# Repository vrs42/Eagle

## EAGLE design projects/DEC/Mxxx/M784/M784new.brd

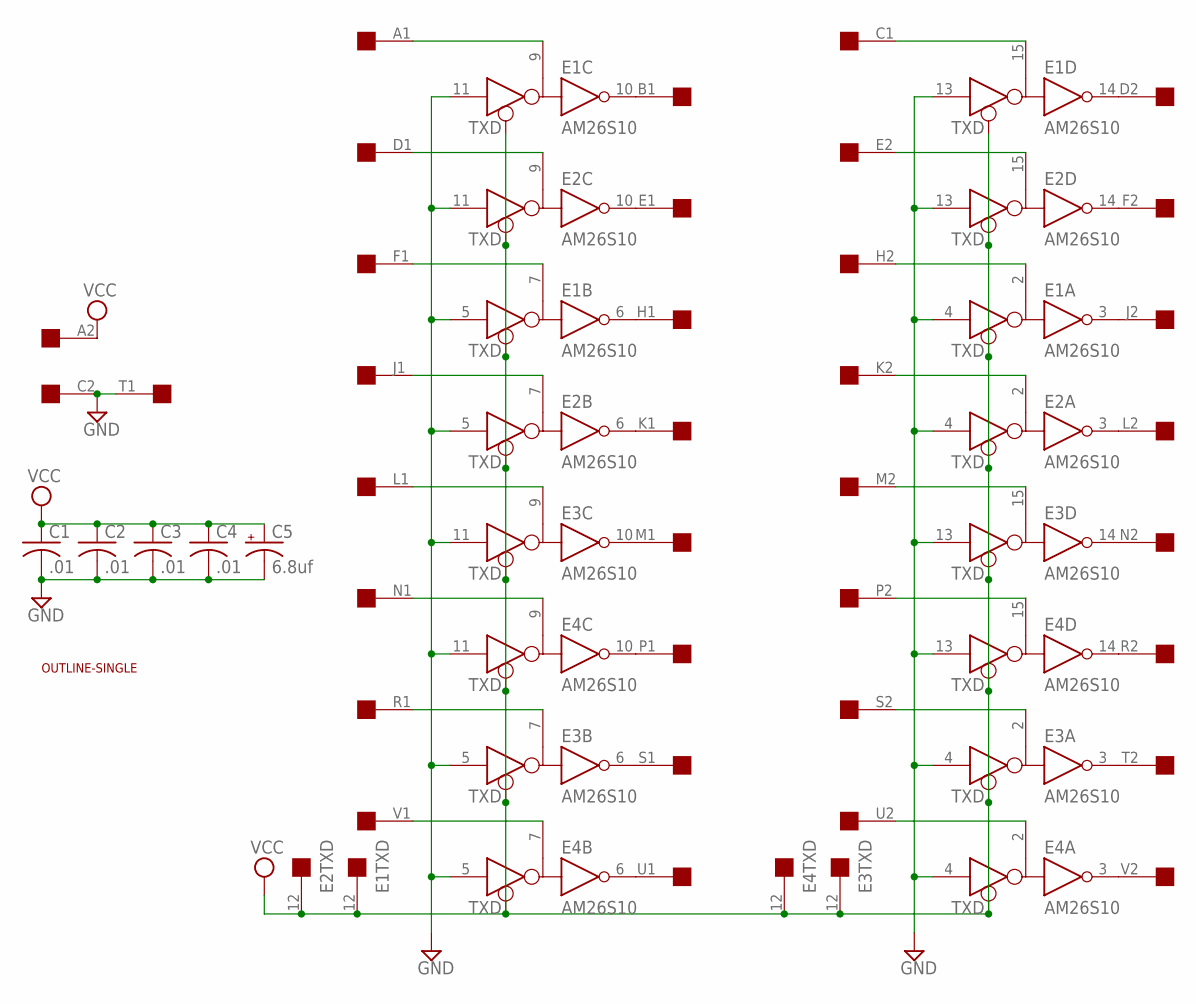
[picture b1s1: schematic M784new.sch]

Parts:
C1, C2, C3, C4: .01; C050-025X075
C5: 6.8uf; E15-5
E1, E2, E3, E4: AM26S10; DIL16
U$1: SINGLE; EDGE-CON2
U$2: OUTLINE-SINGLE; SINGLE

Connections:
GND: C1.2, C2.2, C3.2, C4.2, C5.-, E1.1 (GND), E1.4 (D), E1.5 (D), E1.8 (GND), E1.11 (D), E1.13 (D), E2.1 (GND), E2.4 (D), E2.5 (D), E2.8 (GND), E2.11 (D), E2.13 (D), E3.1 (GND), E3.4 (D), E3.5 (D), E3.8 (GND), E3.11 (D), E3.13 (D), E4.1 (GND), E4.4 (D), E4.5 (D), E4.8 (GND), E4.11 (D), E4.13 (D), U$1.C2, U$1.T1
unnamed: E3.10 (R), U$1.M1
unnamed: E3.9 (B), U$1.L1
unnamed: E2.15 (B), U$1.E2
unnamed: E1.14 (R), U$1.D2
unnamed: E4.9 (B), U$1.N1
unnamed: E1.10 (R), U$1.B1
unnamed: E2.2 (B), U$1.K2
unnamed: E2.10 (R), U$1.E1
unnamed: E2.7 (B), U$1.J1
unnamed: E4.10 (R), U$1.P1
unnamed: E1.6 (R), U$1.H1
unnamed: E4.7 (B), U$1.V1
unnamed: E3.6 (R), U$1.S1
unnamed: E2.14 (R), U$1.F2
unnamed: E3.7 (B), U$1.R1
unnamed: E4.6 (R), U$1.U1
unnamed: E1.15 (B), U$1.C1
unnamed: E1.3 (R), U$1.J2
unnamed: E2.3 (R), U$1.L2
unnamed: E1.2 (B), U$1.H2
unnamed: E3.14 (R), U$1.N2
unnamed: E4.14 (R), U$1.R2
unnamed: E3.3 (R), U$1.T2
unnamed: E4.3 (R), U$1.V2
unnamed: E2.6 (R), U$1.K1
unnamed: E3.15 (B), U$1.M2
unnamed: E4.15 (B), U$1.P2
unnamed: E1.7 (B), U$1.F1
unnamed: E3.2 (B), U$1.S2
unnamed: E2.9 (B), U$1.D1
unnamed: E4.2 (B), U$1.U2
unnamed: E1.9 (B), U$1.A1
VCC: C1.1, C2.1, C3.1, C4.1, C5.+, E1.12 (TXD), E1.16 (VCC), E2.12 (TXD), E2.16 (VCC), E3.12 (TXD), E3.16 (VCC), E4.12 (TXD), E4.16 (VCC), U$1.A2

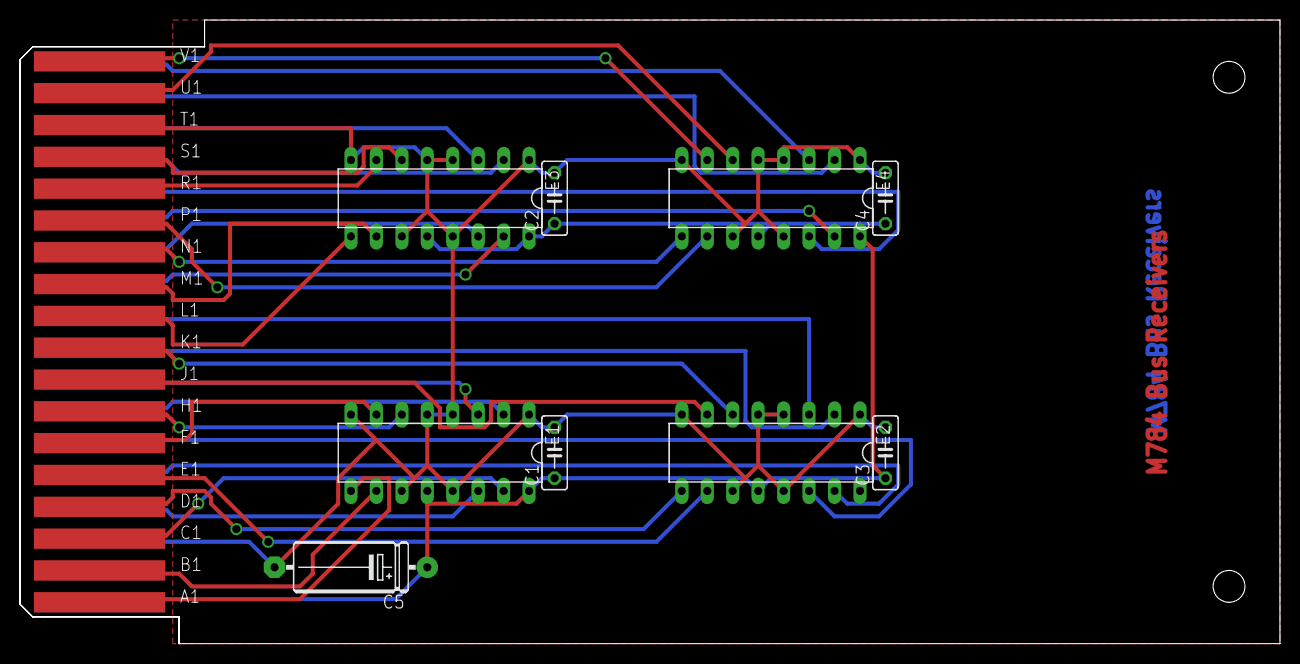
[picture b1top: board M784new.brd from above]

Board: 2 copper layers, 125.7 x 62.2 mm, 11 parts (0 on the bottom side), 34 nets.

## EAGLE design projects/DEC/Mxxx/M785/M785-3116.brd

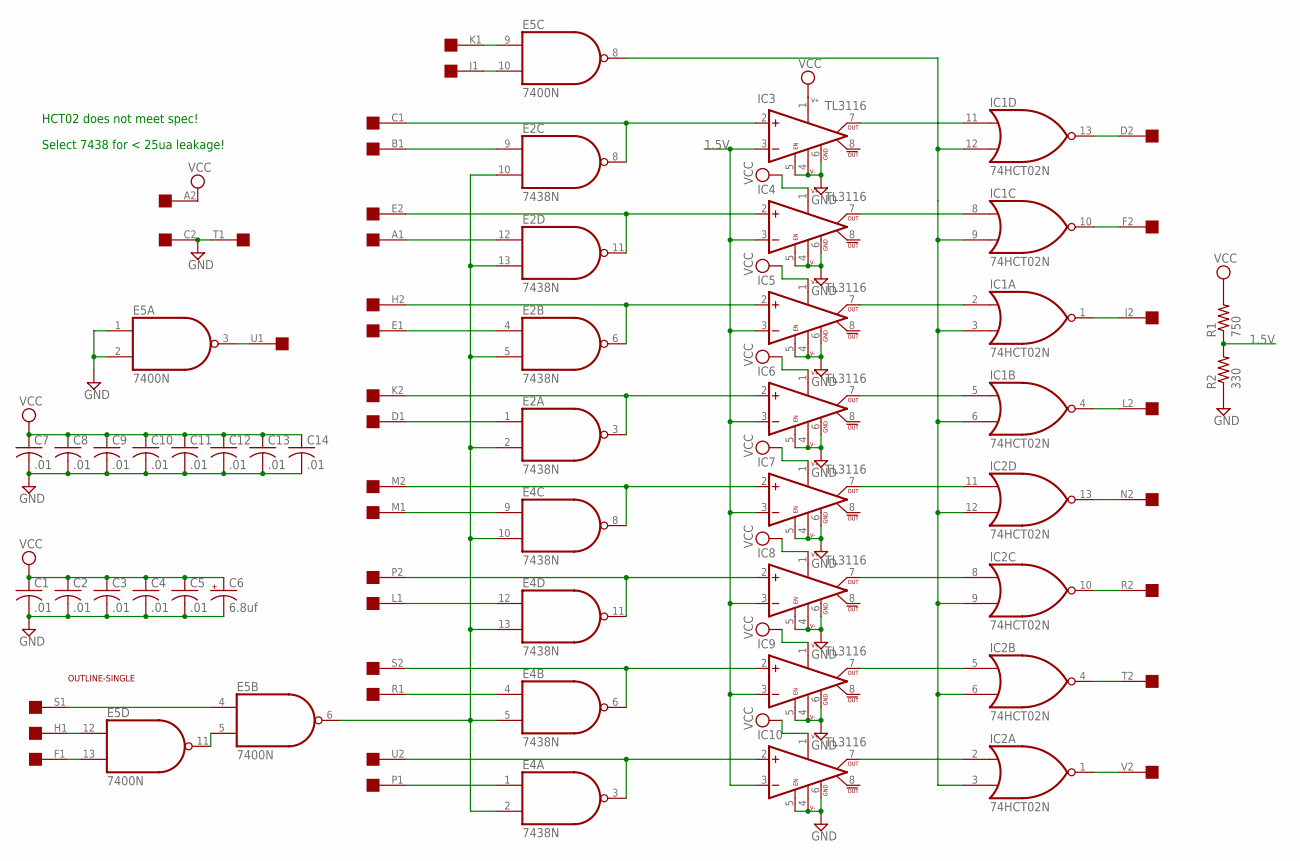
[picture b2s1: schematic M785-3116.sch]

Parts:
C1, C2, C3, C4, C5, C7, C8, C9, C10, C11, C12, C13, C14: .01; C050-025X075
C6: 6.8uf; E15-5
E2, E4: 7438N; DIL14
E5: 7400N; DIL14
IC1, IC2: 74HCT02N; DIL14
IC3, IC4, IC5, IC6, IC7, IC8, IC9, IC10: TL3116; DIL08
R1: 750; 0207/10
R2: 330; 0207/10
U$1: SINGLE; EDGE-CON2
U$2: OUTLINE-SINGLE; SINGLE

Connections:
1.5V: IC3.3 (-IN), IC4.3 (-IN), IC5.3 (-IN), IC6.3 (-IN), IC7.3 (-IN), IC8.3 (-IN), IC9.3 (-IN), IC10.3 (-IN), R1.1, R2.2
GND: C1.2, C2.2, C3.2, C4.2, C5.2, C6.-, C7.2, C8.2, C9.2, C10.2, C11.2, C12.2, C13.2, C14.2, E2.7 (GND), E4.7 (GND), E5.1 (I0), E5.2 (I1), E5.7 (GND), IC1.7 (GND), IC2.7 (GND), IC3.4 (V-), IC3.5 (LA_EN), IC3.6 (GND), IC4.4 (V-), IC4.5 (LA_EN), IC4.6 (GND), IC5.4 (V-), IC5.5 (LA_EN), IC5.6 (GND), IC6.4 (V-), IC6.5 (LA_EN), IC6.6 (GND), IC7.4 (V-), IC7.5 (LA_EN), IC7.6 (GND), IC8.4 (V-), IC8.5 (LA_EN), IC8.6 (GND), IC9.4 (V-), IC9.5 (LA_EN), IC9.6 (GND), IC10.4 (V-), IC10.5 (LA_EN), IC10.6 (GND), R2.1, U$1.C2, U$1.T1
unnamed: E5.8 (O), IC1.3 (I1), IC1.6 (I1), IC1.9 (I1), IC1.12 (I1), IC2.3 (I1), IC2.6 (I1), IC2.9 (I1), IC2.12 (I1)
unnamed: E2.2 (I1), E2.5 (I1), E2.10 (I1), E2.13 (I1), E4.2 (I1), E4.5 (I1), E4.10 (I1), E4.13 (I1), E5.6 (O)
unnamed: E4.8 (O), IC7.2 (+IN), U$1.M2
unnamed: E4.3 (O), IC10.2 (+IN), U$1.U2
unnamed: E4.1 (I0), U$1.P1
unnamed: E4.4 (I0), U$1.R1
unnamed: E4.6 (O), IC9.2 (+IN), U$1.S2
unnamed: E4.12 (I0), U$1.L1
unnamed: E4.11 (O), IC8.2 (+IN), U$1.P2
unnamed: E4.9 (I0), U$1.M1
unnamed: E2.8 (O), IC3.2 (+IN), U$1.C1
unnamed: E2.9 (I0), U$1.B1
unnamed: E2.11 (O), IC4.2 (+IN), U$1.E2
unnamed: E2.12 (I0), U$1.A1
unnamed: E2.6 (O), IC5.2 (+IN), U$1.H2
unnamed: E2.4 (I0), U$1.E1
unnamed: E2.3 (O), IC6.2 (+IN), U$1.K2
unnamed: E2.1 (I0), U$1.D1
unnamed: E5.9 (I0), U$1.K1
unnamed: E5.10 (I1), U$1.J1
unnamed: IC1.13 (O), U$1.D2
unnamed: IC1.10 (O), U$1.F2
unnamed: IC1.1 (O), U$1.J2
unnamed: IC1.4 (O), U$1.L2
unnamed: IC2.13 (O), U$1.N2
unnamed: IC2.10 (O), U$1.R2
unnamed: IC2.4 (O), U$1.T2
unnamed: IC2.1 (O), U$1.V2
unnamed: E5.4 (I0), U$1.S1
unnamed: E5.5 (I1), E5.11 (O)
unnamed: E5.12 (I0), U$1.H1
unnamed: E5.13 (I1), U$1.F1
unnamed: E5.3 (O), U$1.U1
unnamed: IC1.11 (I0), IC3.7 (OUT)
unnamed: IC2.11 (I0), IC7.7 (OUT)
unnamed: IC1.5 (I0), IC6.7 (OUT)
unnamed: IC1.2 (I0), IC5.7 (OUT)
unnamed: IC1.8 (I0), IC4.7 (OUT)
unnamed: IC2.5 (I0), IC9.7 (OUT)
unnamed: IC2.8 (I0), IC8.7 (OUT)
unnamed: IC2.2 (I0), IC10.7 (OUT)
VCC: C1.1, C2.1, C3.1, C4.1, C5.1, C6.+, C7.1, C8.1, C9.1, C10.1, C11.1, C12.1, C13.1, C14.1, E2.14 (VCC), E4.14 (VCC), E5.14 (VCC), IC1.14 (VCC), IC2.14 (VCC), IC3.1 (V+), IC4.1 (V+), IC5.1 (V+), IC6.1 (V+), IC7.1 (V+), IC8.1 (V+), IC9.1 (V+), IC10.1 (V+), R1.2, U$1.A2

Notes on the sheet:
Select 7438 for < 25ua leakage!
HCT02 does not meet spec!

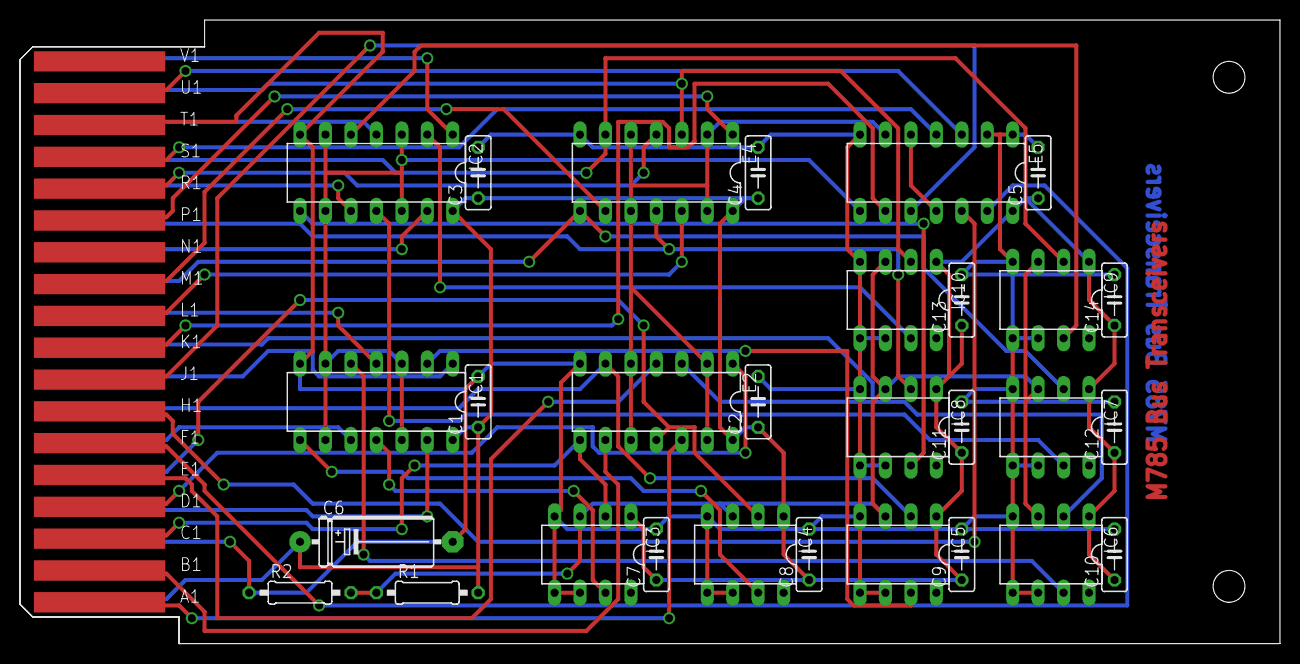
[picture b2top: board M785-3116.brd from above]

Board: 2 copper layers, 125.7 x 62.2 mm, 31 parts (0 on the bottom side), 44 nets.

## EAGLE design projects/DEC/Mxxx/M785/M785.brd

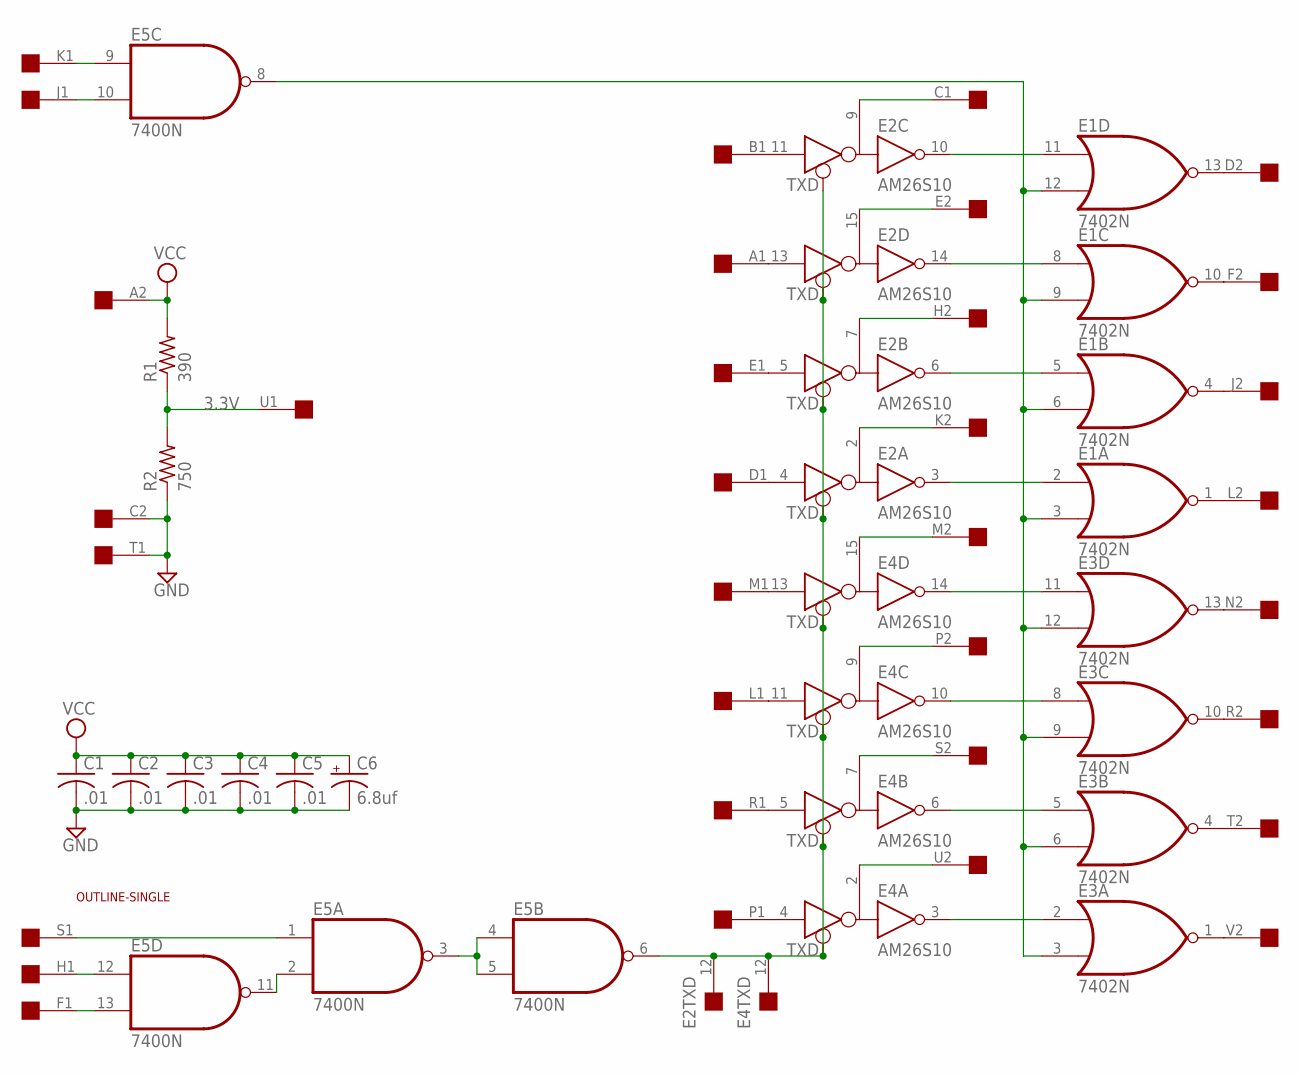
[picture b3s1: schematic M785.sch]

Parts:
C1, C2, C3, C4, C5: .01; C050-025X075
C6: 6.8uf; E15-5
E1, E3: 7402N; DIL14
E2, E4: AM26S10; DIL16
E5: 7400N; DIL14
R1: 390; 0207/10
R2: 750; 0207/10
U$1: SINGLE; EDGE-CON2
U$2: OUTLINE-SINGLE; SINGLE

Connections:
3.3V: R1.1, R2.2, U$1.U1
GND: C1.2, C2.2, C3.2, C4.2, C5.2, C6.-, E1.7 (GND), E2.1 (GND), E2.8 (GND), E3.7 (GND), E4.1 (GND), E4.8 (GND), E5.7 (GND), R2.1, U$1.C2, U$1.T1
unnamed: E2.12 (TXD), E4.12 (TXD), E5.6 (O)
unnamed: E4.15 (B), U$1.M2
unnamed: E4.9 (B), U$1.P2
unnamed: E4.13 (D), U$1.M1
unnamed: E4.11 (D), U$1.L1
unnamed: E4.7 (B), U$1.S2
unnamed: E4.5 (D), U$1.R1
unnamed: E4.2 (B), U$1.U2
unnamed: E4.4 (D), U$1.P1
unnamed: E2.9 (B), U$1.C1
unnamed: E2.11 (D), U$1.B1
unnamed: E2.15 (B), U$1.E2
unnamed: E2.13 (D), U$1.A1
unnamed: E2.7 (B), U$1.H2
unnamed: E2.5 (D), U$1.E1
unnamed: E2.2 (B), U$1.K2
unnamed: E2.4 (D), U$1.D1
unnamed: E5.9 (I0), U$1.K1
unnamed: E5.10 (I1), U$1.J1
unnamed: E1.13 (O), U$1.D2
unnamed: E1.10 (O), U$1.F2
unnamed: E1.4 (O), U$1.J2
unnamed: E1.1 (O), U$1.L2
unnamed: E3.13 (O), U$1.N2
unnamed: E3.10 (O), U$1.R2
unnamed: E3.4 (O), U$1.T2
unnamed: E3.1 (O), U$1.V2
unnamed: E5.1 (I0), U$1.S1
unnamed: E5.2 (I1), E5.11 (O)
unnamed: E5.12 (I0), U$1.H1
unnamed: E5.13 (I1), U$1.F1
unnamed: E1.3 (I1), E1.6 (I1), E1.9 (I1), E1.12 (I1), E3.3 (I1), E3.6 (I1), E3.9 (I1), E3.12 (I1), E5.8 (O)
unnamed: E3.2 (I0), E4.3 (R)
unnamed: E3.5 (I0), E4.6 (R)
unnamed: E3.8 (I0), E4.10 (R)
unnamed: E3.11 (I0), E4.14 (R)
unnamed: E1.2 (I0), E2.3 (R)
unnamed: E1.5 (I0), E2.6 (R)
unnamed: E1.8 (I0), E2.14 (R)
unnamed: E1.11 (I0), E2.10 (R)
unnamed: E5.3 (O), E5.4 (I0), E5.5 (I1)
VCC: C1.1, C2.1, C3.1, C4.1, C5.1, C6.+, E1.14 (VCC), E2.16 (VCC), E3.14 (VCC), E4.16 (VCC), E5.14 (VCC), R1.2, U$1.A2

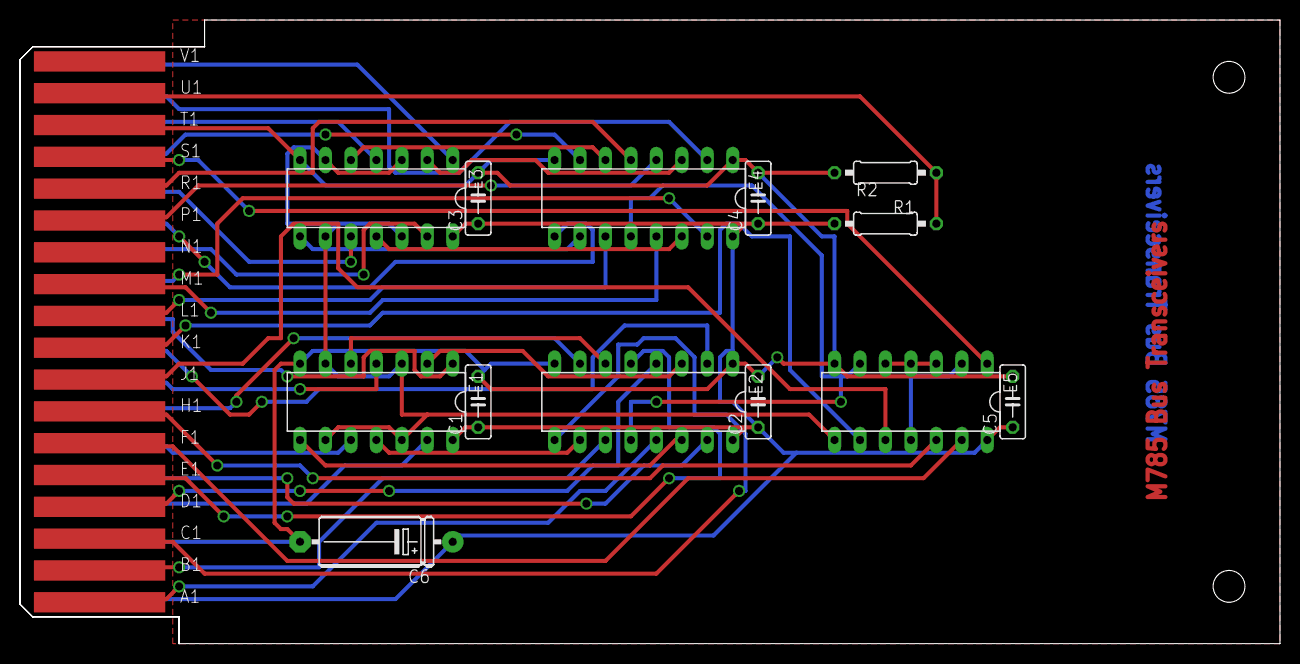
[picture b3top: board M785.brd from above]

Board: 2 copper layers, 125.7 x 62.2 mm, 15 parts (0 on the bottom side), 44 nets.

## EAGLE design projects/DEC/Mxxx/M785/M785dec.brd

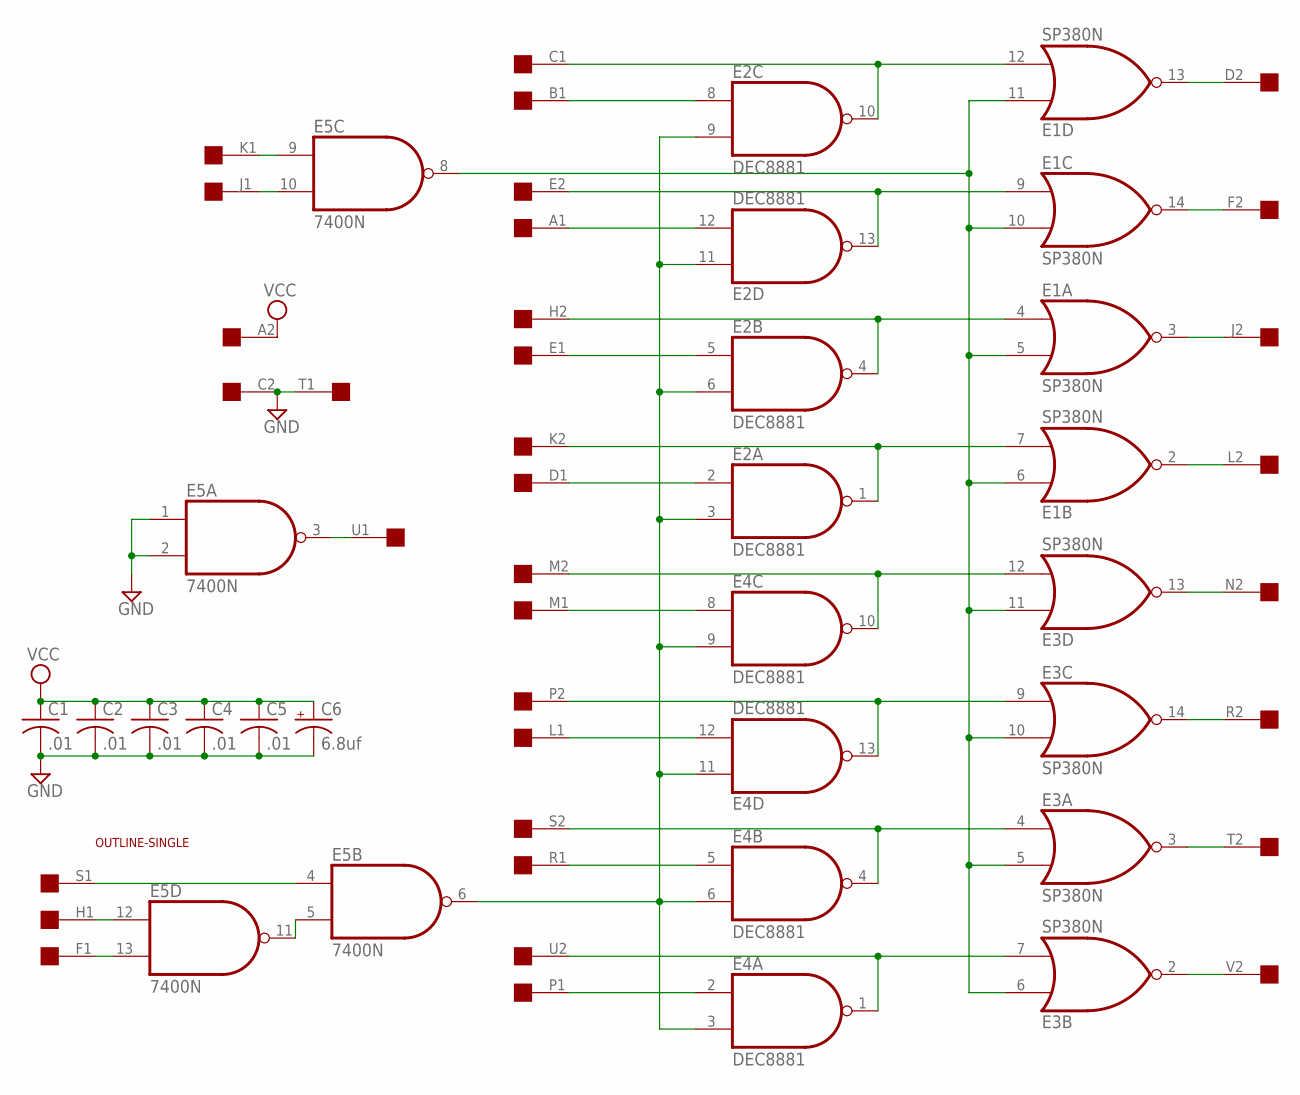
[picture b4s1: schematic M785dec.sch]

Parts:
C1, C2, C3, C4, C5: .01; C050-025X075
C6: 6.8uf; E15-5
E1, E3: SP380N; DIL14
E2, E4: DEC8881; DIL14
E5: 7400N; DIL14
U$1: SINGLE; EDGE-CON2
U$2: OUTLINE-SINGLE; SINGLE

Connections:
GND: C1.2, C2.2, C3.2, C4.2, C5.2, C6.-, E1.1 (GND), E2.7 (GND), E3.1 (GND), E4.7 (GND), E5.1 (I0), E5.2 (I1), E5.7 (GND), U$1.C2, U$1.T1
unnamed: E1.5 (I1), E1.6 (I0), E1.10 (I1), E1.11 (I0), E3.5 (I1), E3.6 (I0), E3.10 (I1), E3.11 (I0), E5.8 (O)
unnamed: E2.3 (I1), E2.6 (I1), E2.9 (I1), E2.11 (I0), E4.3 (I1), E4.6 (I1), E4.9 (I1), E4.11 (I0), E5.6 (O)
unnamed: E3.12 (I1), E4.10 (O), U$1.M2
unnamed: E3.7 (I1), E4.1 (O), U$1.U2
unnamed: E4.2 (I0), U$1.P1
unnamed: E4.5 (I0), U$1.R1
unnamed: E3.4 (I0), E4.4 (O), U$1.S2
unnamed: E4.12 (I1), U$1.L1
unnamed: E3.9 (I0), E4.13 (O), U$1.P2
unnamed: E4.8 (I0), U$1.M1
unnamed: E1.12 (I1), E2.10 (O), U$1.C1
unnamed: E2.8 (I0), U$1.B1
unnamed: E1.9 (I0), E2.13 (O), U$1.E2
unnamed: E2.12 (I1), U$1.A1
unnamed: E1.4 (I0), E2.4 (O), U$1.H2
unnamed: E2.5 (I0), U$1.E1
unnamed: E1.7 (I1), E2.1 (O), U$1.K2
unnamed: E2.2 (I0), U$1.D1
unnamed: E5.9 (I0), U$1.K1
unnamed: E5.10 (I1), U$1.J1
unnamed: E1.13 (O), U$1.D2
unnamed: E1.14 (O), U$1.F2
unnamed: E1.3 (O), U$1.J2
unnamed: E1.2 (O), U$1.L2
unnamed: E3.13 (O), U$1.N2
unnamed: E3.14 (O), U$1.R2
unnamed: E3.3 (O), U$1.T2
unnamed: E3.2 (O), U$1.V2
unnamed: E5.4 (I0), U$1.S1
unnamed: E5.5 (I1), E5.11 (O)
unnamed: E5.12 (I0), U$1.H1
unnamed: E5.13 (I1), U$1.F1
unnamed: E5.3 (O), U$1.U1
VCC: C1.1, C2.1, C3.1, C4.1, C5.1, C6.+, E1.8 (VCC), E2.14 (VCC), E3.8 (VCC), E4.14 (VCC), E5.14 (VCC), U$1.A2

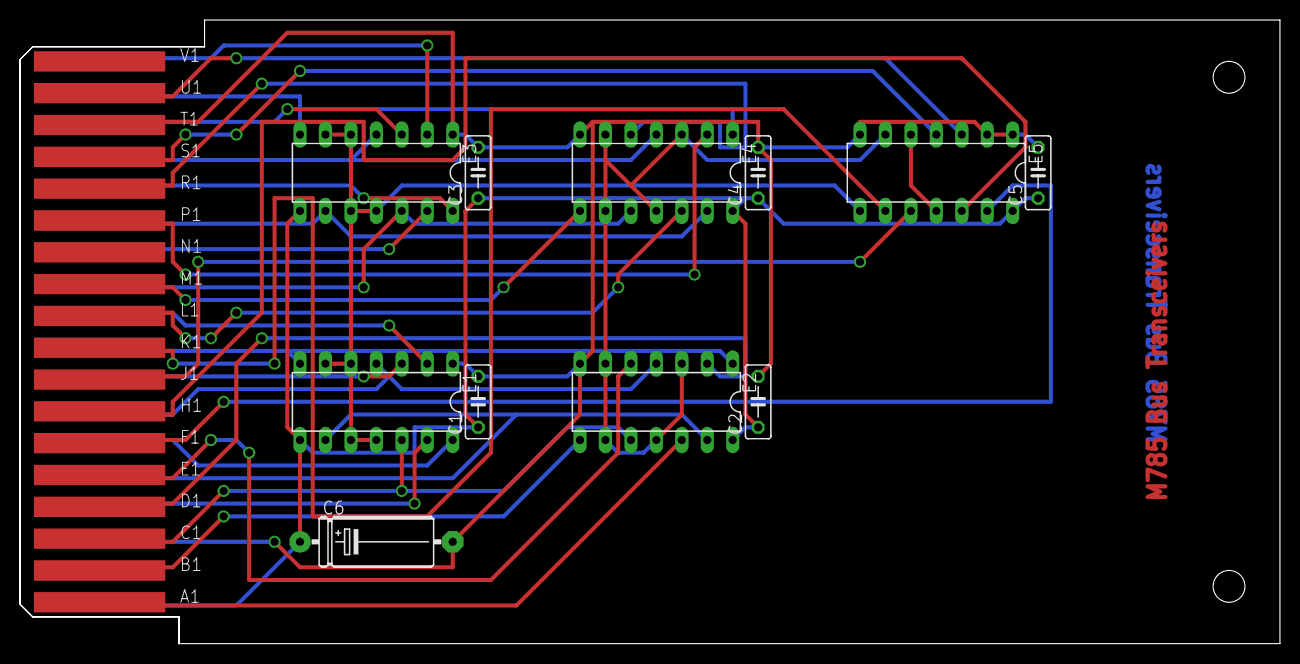
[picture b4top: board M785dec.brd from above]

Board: 2 copper layers, 125.7 x 62.2 mm, 13 parts (0 on the bottom side), 35 nets.

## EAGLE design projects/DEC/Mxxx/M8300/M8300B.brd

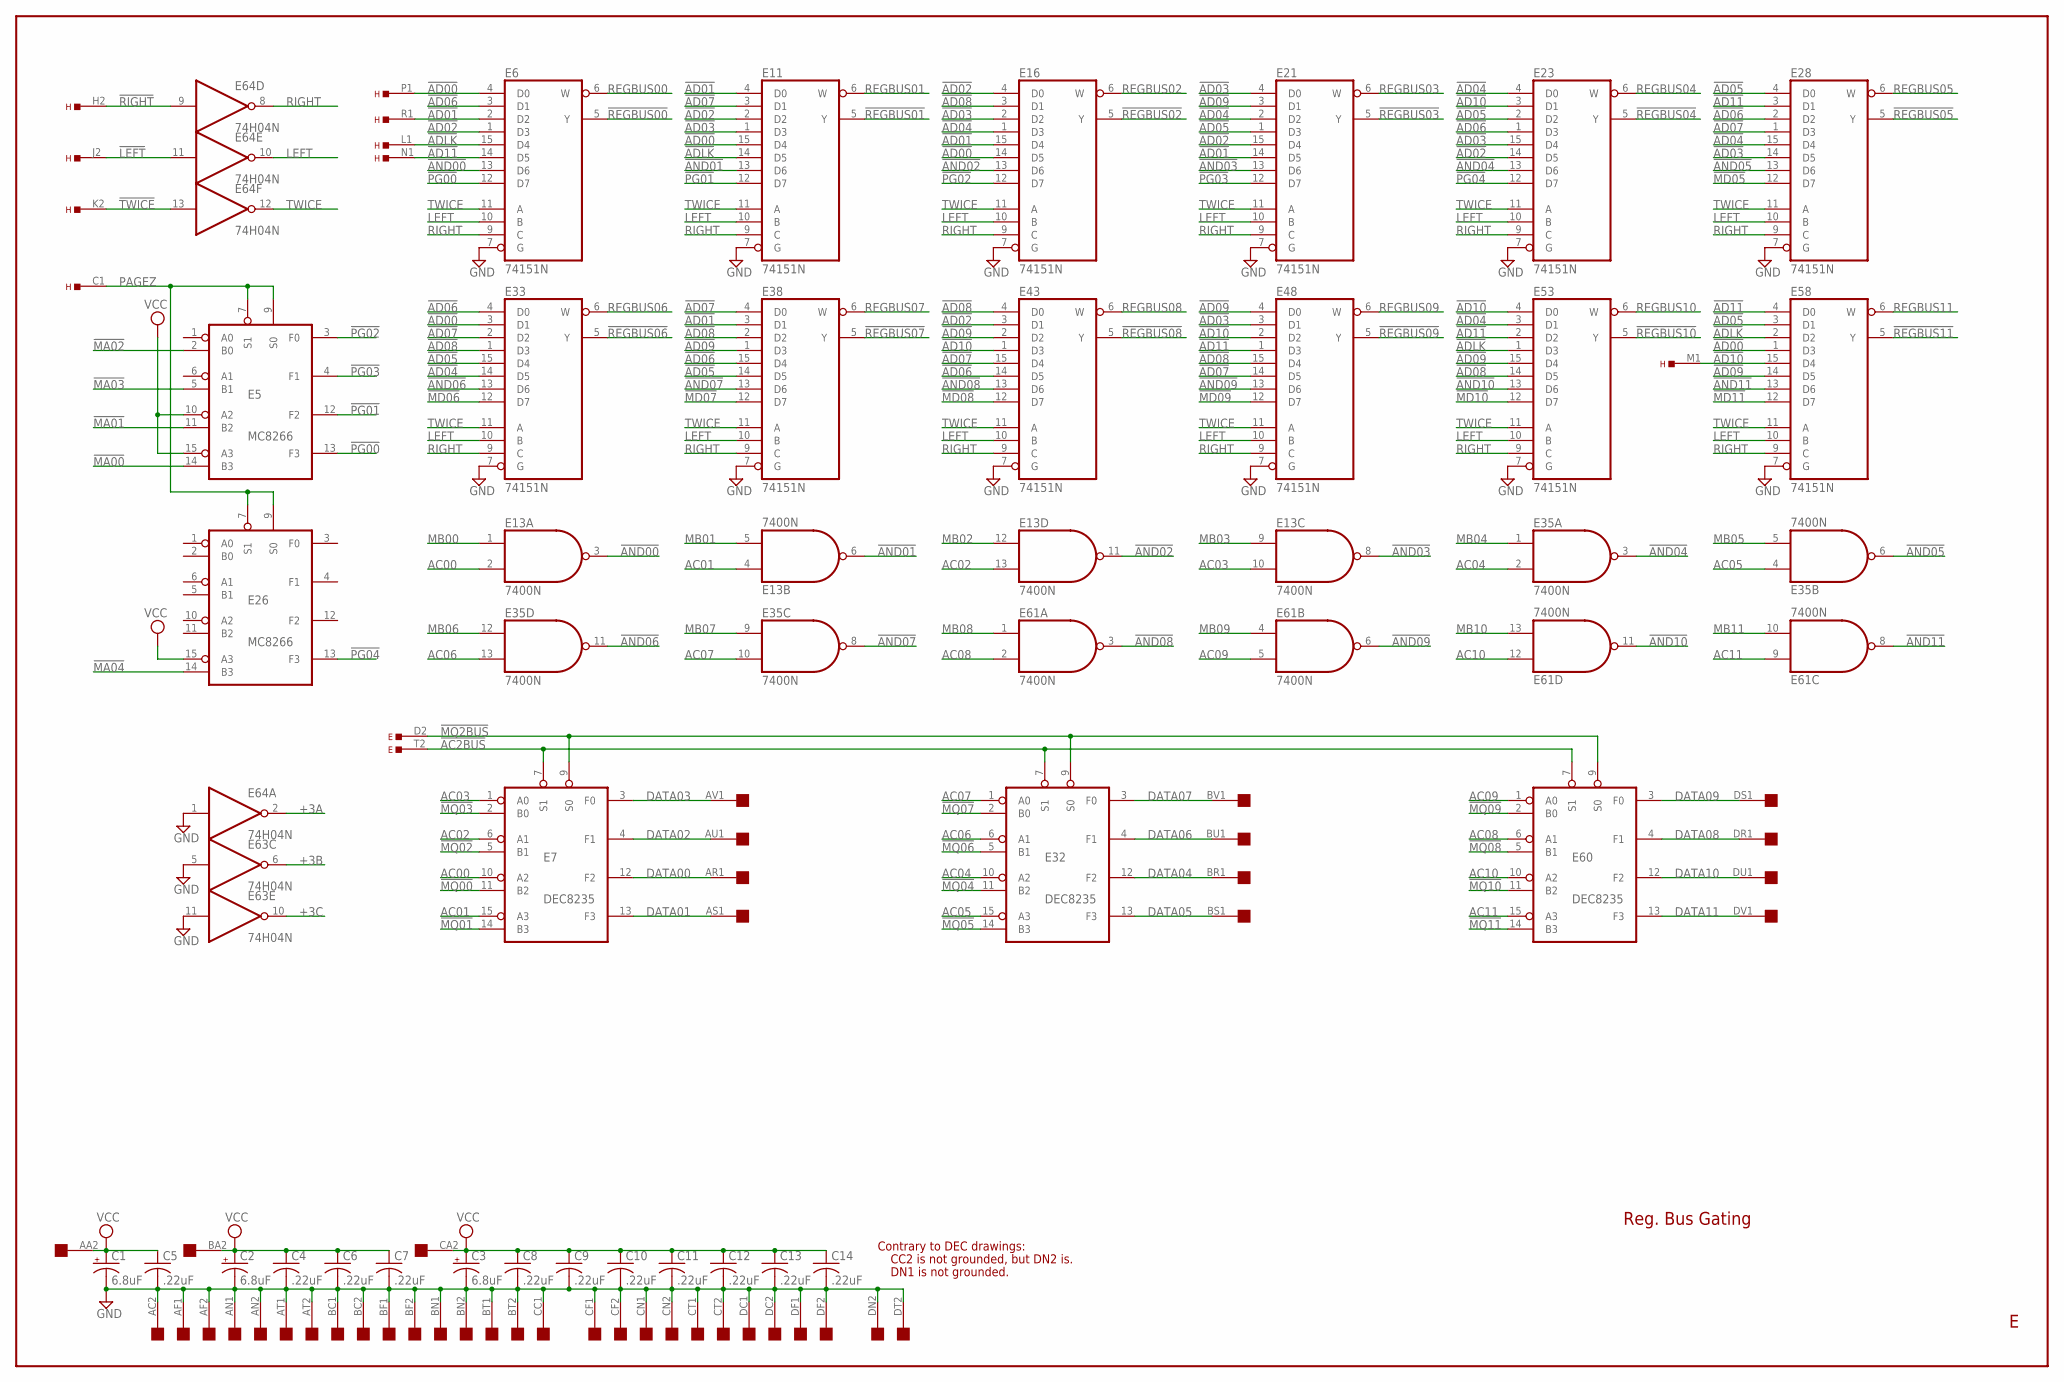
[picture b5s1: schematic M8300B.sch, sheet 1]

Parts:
C1, C2, C3: 6.8uF; E12-8
C4, C5, C6, C7, C8, C9, C10, C11, C12, C13, C14: .22uF; C063-025X075
E: EDGE-TOP; EDGE-CON2
E5, E26: MC8266; DIL16
E6, E11, E16, E21, E23, E28, E33, E38, E43, E48, E53, E58: 74151N; DIL16
E7, E32, E60: DEC8235; DIL16
E13, E35, E61: 7400N; DIL14
E63, E64: 74H04N; DIL14
H: EDGE-TOP; EDGE-CON2
U$2: QUAD; EDGE-CON8

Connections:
!AC2BUS: E.T2, E7.7 (S1), E32.7 (S1), E60.7 (S1)
!AD00: E6.4 (D0), E11.15 (D4), E16.14 (D5), E33.3 (D1), E58.1 (D3), H.P1; also elsewhere on the board
!AD01: E6.2 (D2), E11.4 (D0), E16.15 (D4), E21.14 (D5), E38.3 (D1), H.R1; also elsewhere on the board
!AD02: E6.1 (D3), E11.2 (D2), E16.4 (D0), E21.15 (D4), E23.14 (D5), E43.3 (D1); also elsewhere on the board
!AD03: E11.1 (D3), E16.2 (D2), E21.4 (D0), E23.15 (D4), E28.14 (D5), E48.3 (D1); also elsewhere on the board
!AD04: E16.1 (D3), E21.2 (D2), E23.4 (D0), E28.15 (D4), E33.14 (D5), E53.3 (D1); also elsewhere on the board
!AD05: E21.1 (D3), E23.2 (D2), E28.4 (D0), E33.15 (D4), E38.14 (D5), E58.3 (D1); also elsewhere on the board
!AD06: E6.3 (D1), E23.1 (D3), E28.2 (D2), E33.4 (D0), E38.15 (D4), E43.14 (D5); also elsewhere on the board
!AD07: E11.3 (D1), E28.1 (D3), E33.2 (D2), E38.4 (D0), E43.15 (D4), E48.14 (D5); also elsewhere on the board
!AD08: E16.3 (D1), E33.1 (D3), E38.2 (D2), E43.4 (D0), E48.15 (D4), E53.14 (D5); also elsewhere on the board
!AD09: E21.3 (D1), E38.1 (D3), E43.2 (D2), E48.4 (D0), E53.15 (D4), E58.14 (D5); also elsewhere on the board
!AD10: E23.3 (D1), E43.1 (D3), E48.2 (D2), E53.4 (D0), E58.15 (D4), H.M1; also elsewhere on the board
!AD11: E6.14 (D5), E28.3 (D1), E48.1 (D3), E53.2 (D2), E58.4 (D0), H.N1; also elsewhere on the board
!ADLK: E6.15 (D4), E11.14 (D5), E53.1 (D3), E58.2 (D2), H.L1
!AND00: E6.13 (D6), E13.3 (O)
!AND01: E11.13 (D6), E13.6 (O)
!AND02: E13.11 (O), E16.13 (D6)
!AND03: E13.8 (O), E21.13 (D6)
!AND04: E23.13 (D6), E35.3 (O)
!AND05: E28.13 (D6), E35.6 (O)
!AND06: E33.13 (D6), E35.11 (O)
!AND07: E35.8 (O), E38.13 (D6)
!AND08: E43.13 (D6), E61.3 (O)
!AND09: E48.13 (D6), E61.6 (O)
!AND10: E53.13 (D6), E61.11 (O)
!AND11: E58.13 (D6), E61.8 (O)
!LEFT: E64.11 (I), H.J2
!MA00: E5.14 (B3); also elsewhere on the board
!MA01: E5.11 (B2); also elsewhere on the board
!MA02: E5.2 (B0); also elsewhere on the board
!MA03: E5.5 (B1); also elsewhere on the board
!MA04: E26.14 (B3); also elsewhere on the board
!MD05: E28.12 (D7); also elsewhere on the board
!MD06: E33.12 (D7); also elsewhere on the board
!MD07: E38.12 (D7); also elsewhere on the board
!MD08: E43.12 (D7); also elsewhere on the board
!MD09: E48.12 (D7); also elsewhere on the board
!MD10: E53.12 (D7); also elsewhere on the board
!MD11: E58.12 (D7); also elsewhere on the board
!MQ00: E7.11 (B2); also elsewhere on the board
!MQ01: E7.14 (B3); also elsewhere on the board
!MQ02: E7.5 (B1); also elsewhere on the board
!MQ2BUS: E.D2, E7.9 (S0), E32.9 (S0), E60.9 (S0)
!MQ03: E7.2 (B0); also elsewhere on the board
!MQ04: E32.11 (B2); also elsewhere on the board
!MQ05: E32.14 (B3); also elsewhere on the board
!MQ06: E32.5 (B1); also elsewhere on the board
!MQ07: E32.2 (B0); also elsewhere on the board
!MQ08: E60.5 (B1); also elsewhere on the board
!MQ09: E60.2 (B0); also elsewhere on the board
!MQ10: E60.11 (B2); also elsewhere on the board
!MQ11: E60.14 (B3); also elsewhere on the board
!PG00: E5.13 (F3), E6.12 (D7)
!PG01: E5.12 (F2), E11.12 (D7)
!PG02: E5.3 (F0), E16.12 (D7)
!PG03: E5.4 (F1), E21.12 (D7)
!PG04: E23.12 (D7), E26.13 (F3)
!REGBUS00: E6.5 (Y); also elsewhere on the board
!REGBUS01: E11.5 (Y); also elsewhere on the board
!REGBUS02: E16.5 (Y); also elsewhere on the board
!REGBUS03: E21.5 (Y); also elsewhere on the board
!REGBUS04: E23.5 (Y); also elsewhere on the board
!REGBUS05: E28.5 (Y); also elsewhere on the board
!REGBUS06: E33.5 (Y); also elsewhere on the board
!REGBUS07: E38.5 (Y); also elsewhere on the board
!REGBUS08: E43.5 (Y); also elsewhere on the board
!REGBUS09: E48.5 (Y); also elsewhere on the board
!REGBUS10: E53.5 (Y); also elsewhere on the board
!REGBUS11: E58.5 (Y); also elsewhere on the board
!RIGHT: E64.9 (I), H.H2; also elsewhere on the board
!TWICE: E64.13 (I), H.K2
+3A: E64.2 (O); also elsewhere on the board
+3B: E63.6 (O); also elsewhere on the board
+3C: E63.10 (O); also elsewhere on the board
AC00: E7.10 (A2), E13.2 (I1); also elsewhere on the board
AC01: E7.15 (A3), E13.4 (I0); also elsewhere on the board
AC02: E7.6 (A1), E13.13 (I1); also elsewhere on the board
AC03: E7.1 (A0), E13.10 (I1); also elsewhere on the board
AC04: E32.10 (A2), E35.2 (I1); also elsewhere on the board
AC05: E32.15 (A3), E35.4 (I0); also elsewhere on the board
AC06: E32.6 (A1), E35.13 (I1); also elsewhere on the board
AC07: E32.1 (A0), E35.10 (I1); also elsewhere on the board
AC08: E60.6 (A1), E61.2 (I1); also elsewhere on the board
AC09: E60.1 (A0), E61.5 (I1); also elsewhere on the board
AC10: E60.10 (A2), E61.12 (I0); also elsewhere on the board
AC11: E60.15 (A3), E61.9 (I0); also elsewhere on the board
DATA00: E7.12 (F2), U$2.AR1; also elsewhere on the board
DATA01: E7.13 (F3), U$2.AS1; also elsewhere on the board
DATA02: E7.4 (F1), U$2.AU1; also elsewhere on the board
DATA03: E7.3 (F0), U$2.AV1; also elsewhere on the board
DATA04: E32.12 (F2), U$2.BR1; also elsewhere on the board
DATA05: E32.13 (F3), U$2.BS1; also elsewhere on the board
DATA06: E32.4 (F1), U$2.BU1; also elsewhere on the board
DATA07: E32.3 (F0), U$2.BV1; also elsewhere on the board
DATA08: E60.4 (F1), U$2.DR1; also elsewhere on the board
DATA09: E60.3 (F0), U$2.DS1; also elsewhere on the board
DATA10: E60.12 (F2), U$2.DU1; also elsewhere on the board
DATA11: E60.13 (F3), U$2.DV1; also elsewhere on the board
GND: C1.-, C2.-, C3.-, C4.2, C5.2, C6.2, C7.2, C8.2, C9.2, C10.2, C11.2, C12.2, C13.2, C14.2, E5.8 (GND), E6.7 (G), E6.8 (GND), E7.8 (GND), E11.7 (G), E11.8 (GND), E13.7 (GND), E16.7 (G), E16.8 (GND), E21.7 (G), E21.8 (GND), E23.7 (G), E23.8 (GND), E26.8 (GND), E28.7 (G), E28.8 (GND), E32.8 (GND), E33.7 (G), E33.8 (GND), E35.7 (GND), E38.7 (G), E38.8 (GND), E43.7 (G), E43.8 (GND), E48.7 (G), E48.8 (GND), E53.7 (G), E53.8 (GND), E58.7 (G), E58.8 (GND), E60.8 (GND), E61.7 (GND), E63.5 (I), E63.7 (GND), E63.11 (I), E64.1 (I), E64.7 (GND), U$2.AC2, U$2.AF1, U$2.AF2, U$2.AN1, U$2.AN2, U$2.AT1, U$2.AT2, U$2.BC1, U$2.BC2, U$2.BF1, U$2.BF2, U$2.BN1, U$2.BN2, U$2.BT1, U$2.BT2, U$2.CC1, U$2.CF1, U$2.CF2, U$2.CN1, U$2.CN2, U$2.CT1, U$2.CT2, U$2.DC1, U$2.DC2, U$2.DF1, U$2.DF2, U$2.DN2, U$2.DT2; also elsewhere on the board
LEFT: E6.10 (B), E11.10 (B), E16.10 (B), E21.10 (B), E23.10 (B), E28.10 (B), E33.10 (B), E38.10 (B), E43.10 (B), E48.10 (B), E53.10 (B), E58.10 (B), E64.10 (O)
MB00: E13.1 (I0); also elsewhere on the board
MB01: E13.5 (I1); also elsewhere on the board
MB02: E13.12 (I0); also elsewhere on the board
MB03: E13.9 (I0); also elsewhere on the board
MB04: E35.1 (I0); also elsewhere on the board
MB05: E35.5 (I1); also elsewhere on the board
MB06: E35.12 (I0); also elsewhere on the board
MB07: E35.9 (I0); also elsewhere on the board
MB08: E61.1 (I0); also elsewhere on the board
MB09: E61.4 (I0); also elsewhere on the board
MB10: E61.13 (I1); also elsewhere on the board
MB11: E61.10 (I1); also elsewhere on the board
PAGEZ: E5.7 (S1), E5.9 (S0), E26.7 (S1), E26.9 (S0), H.C1
REGBUS00: E6.6 (W); also elsewhere on the board
REGBUS01: E11.6 (W); also elsewhere on the board
REGBUS02: E16.6 (W); also elsewhere on the board
REGBUS03: E21.6 (W); also elsewhere on the board
REGBUS04: E23.6 (W); also elsewhere on the board
REGBUS05: E28.6 (W); also elsewhere on the board
REGBUS06: E33.6 (W); also elsewhere on the board
REGBUS07: E38.6 (W); also elsewhere on the board
REGBUS08: E43.6 (W); also elsewhere on the board
REGBUS09: E48.6 (W); also elsewhere on the board
REGBUS10: E53.6 (W); also elsewhere on the board
REGBUS11: E58.6 (W); also elsewhere on the board
RIGHT: E6.9 (C), E11.9 (C), E16.9 (C), E21.9 (C), E23.9 (C), E28.9 (C), E33.9 (C), E38.9 (C), E43.9 (C), E48.9 (C), E53.9 (C), E58.9 (C), E64.8 (O)
TWICE: E6.11 (A), E11.11 (A), E16.11 (A), E21.11 (A), E23.11 (A), E28.11 (A), E33.11 (A), E38.11 (A), E43.11 (A), E48.11 (A), E53.11 (A), E58.11 (A), E64.12 (O)
VCC: C1.+, C2.+, C3.+, C4.1, C5.1, C6.1, C7.1, C8.1, C9.1, C10.1, C11.1, C12.1, C13.1, C14.1, E5.10 (A2), E5.15 (A3), E5.16 (VCC), E6.16 (VCC), E7.16 (VCC), E11.16 (VCC), E13.14 (VCC), E16.16 (VCC), E21.16 (VCC), E23.16 (VCC), E26.15 (A3), E26.16 (VCC), E28.16 (VCC), E32.16 (VCC), E33.16 (VCC), E35.14 (VCC), E38.16 (VCC), E43.16 (VCC), E48.16 (VCC), E53.16 (VCC), E58.16 (VCC), E60.16 (VCC), E61.14 (VCC), E63.14 (VCC), E64.14 (VCC), U$2.AA2, U$2.BA2, U$2.CA2; also elsewhere on the board

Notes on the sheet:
CC2 is not grounded, but DN2 is.
Contrary to DEC drawings:
DN1 is not grounded.
Reg. Bus Gating
